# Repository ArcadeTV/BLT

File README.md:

## BLT (Button Layout Toggler)
### v20221101
#### ArcadeTV

| Part | Value            | Device           | Package             |
| ---- | ---------------- | ---------------- | ------------------- |
| CB1  | 100nF            | C-USC0805        | C0805               |
| CB2  | 100nF            | C-USC0805        | C0805               |
| CB3  | 100nF            | C-USC0805        | C0805               |
| D1   |                  | DUOLED2X5        | DUOLED2X5           |
| IC1  | 74HC4066D        | 74HC4066D        | SOIC127P600X175-14N |
| IC2  | 74HC4066D        | 74HC4066D        | SOIC127P600X175-14N |
| IC3  | ATTINY84V-10SSUR | ATTINY84V-10SSUR | SOIC127P600X175-14N |
| R1   | 220              | R-US_R0805       | R0805               |
| R2   | 220              | R-US_R0805       | R0805               |

---

#### Description:
This pcb remaps 4 buttons of a common-ground controller to two different layouts,
given that your controller has a 6-button-layout.
I was tired of having to reconfigure my arcade stick every time I switched games between
Street Fighter (6 Buttons) and Neo Geo (4 Buttons), so I came up with a solution that 
goes between the first four input signal lines from either a supergun or jamma harness.
The toggler pad on the pcb goes to a switch that connects to GND. This will trigger
the switching process and visual feedback can be added by an optional 2-color-LED.
Buttons 5 and 6 are not involved.

#### Microcontroller:
Please mind that the ATtiny84 microcontroller needs to be programmed
with the provided hex file.

#### PCB
Use the provided gerber files from the [releases tab](https://github.com/ArcadeTV/BLT/releases/latest) to order your pcb from your favorite manufacturer.

Eagle source files for editing also exist in this repository.

#### Installation
Populate the pcb after programming the ATtiny microcontroller.
Connect the lines coming from your supergun or jamma harness to the pads
marked with IN. Connect the button-lines to the pads marked OUT.
Connect a switch to the toggler-pad on the upper right of the pcb that
connects temporary to GND upon being pressed.
Install a 2-color-LED as you see fit. (Adjust R1 and R2 according to your LED specs)

```
Layout #1 (Street Fighter Style):
   .-.   .-.   .-.
  ( 1 ) ( 2 ) ( 3 )
   '-'   '-'   '-'
 .-.   .-.   .-.
( 4 ) ( 5 ) ( 6 )
 '-'   '-'   '-'

Layout #2 (Neo Geo Style):
   .-.   .-.   .-.
  ( 2 ) ( 3 ) ( 4 )
   '-'   '-'   '-'
 .-.   .-.   .-.
( 1 ) ( 5 ) ( 6 )
 '-'   '-'   '-'

```

Tested on a HORI Fighting Stick V3 (PS3 Version) that was rewired with a DB15 cable and connector
for use with a MINIGUN v2.5. The PS button on that stick was wired for toggling.

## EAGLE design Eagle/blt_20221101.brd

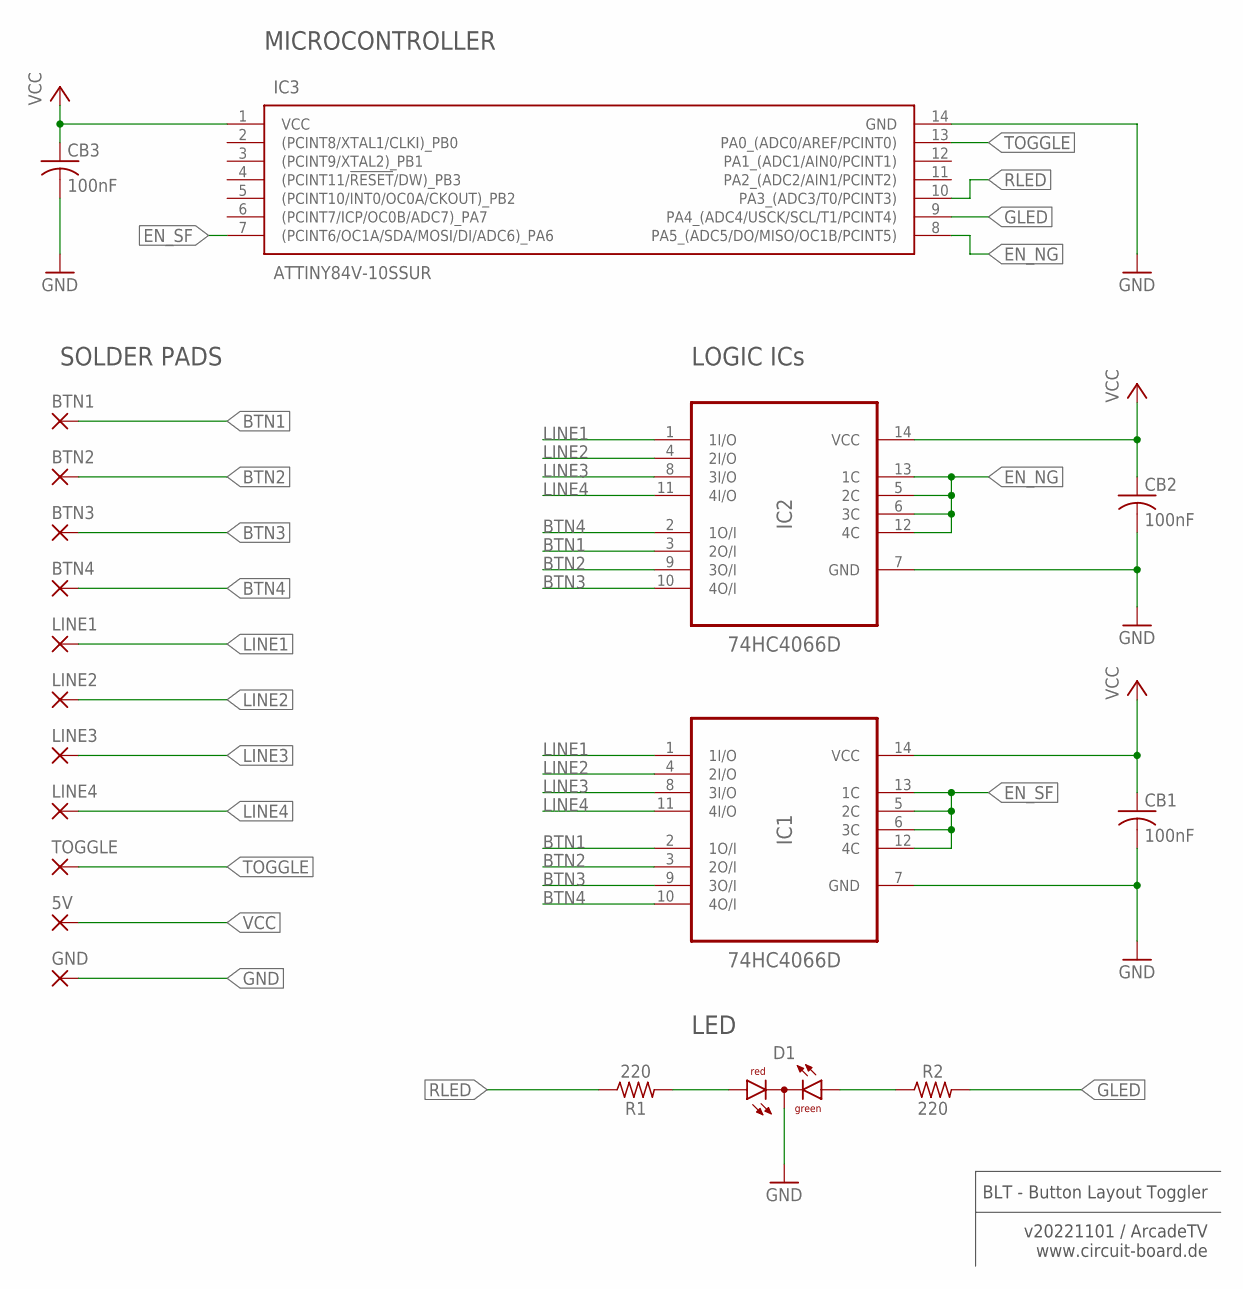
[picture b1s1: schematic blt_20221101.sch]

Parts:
5V: WIREPADSMD2,54-5,08; SMD2,54-5,08
BTN1, BTN2, BTN3, BTN4: WIREPADSMD2,54-5,08; SMD2,54-5,08
CB1, CB2, CB3: 100nF; C0805
D1: DUOLED2X5
GND: WIREPADSMD2,54-5,08; SMD2,54-5,08
IC1, IC2: 74HC4066D; SOIC127P600X175-14N
IC3: ATTINY84V-10SSUR; SOIC127P600X175-14N
LINE1, LINE2, LINE3, LINE4: WIREPADSMD2,54-5,08; SMD2,54-5,08
R1, R2: 220; R0805
TOGGLE: WIREPADSMD2,54-5,08; SMD2,54-5,08

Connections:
BTN1: BTN1.1, IC1.2 (1O/I), IC2.3 (2O/I)
BTN2: BTN2.1, IC1.3 (2O/I), IC2.9 (3O/I)
BTN3: BTN3.1, IC1.9 (3O/I), IC2.10 (4O/I)
BTN4: BTN4.1, IC1.10 (4O/I), IC2.2 (1O/I)
EN_NG: IC2.5 (2C), IC2.6 (3C), IC2.12 (4C), IC2.13 (1C), IC3.8 (PA5_(ADC5/DO/MISO/OC1B/PCINT5))
EN_SF: IC1.5 (2C), IC1.6 (3C), IC1.12 (4C), IC1.13 (1C), IC3.7 ((PCINT6/OC1A/SDA/MOSI/DI/ADC6)_PA6)
GLED: IC3.9 (PA4_(ADC4/USCK/SCL/T1/PCINT4)), R2.2
GND: CB1.2, CB2.2, CB3.2, D1.K (C), GND.1, IC1.7 (GND), IC2.7 (GND), IC3.14 (GND)
LINE1: IC1.1 (1I/O), IC2.1 (1I/O), LINE1.1
LINE2: IC1.4 (2I/O), IC2.4 (2I/O), LINE2.1
LINE3: IC1.8 (3I/O), IC2.8 (3I/O), LINE3.1
LINE4: IC1.11 (4I/O), IC2.11 (4I/O), LINE4.1
unnamed: D1.AR, R1.2
unnamed: D1.AG, R2.1
RLED: IC3.10 (PA3_(ADC3/T0/PCINT3)), R1.1
TOGGLE: IC3.13 (PA0_(ADC0/AREF/PCINT0)), TOGGLE.1
VCC: 5V.1, CB1.1, CB2.1, CB3.1, IC1.14 (VCC), IC2.14 (VCC), IC3.1 (VCC)

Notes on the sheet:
BLT - Button Layout Toggler v20221101 / ArcadeTV www.circuit-board.de
MICROCONTROLLER
SOLDER PADS
LOGIC ICs
LED

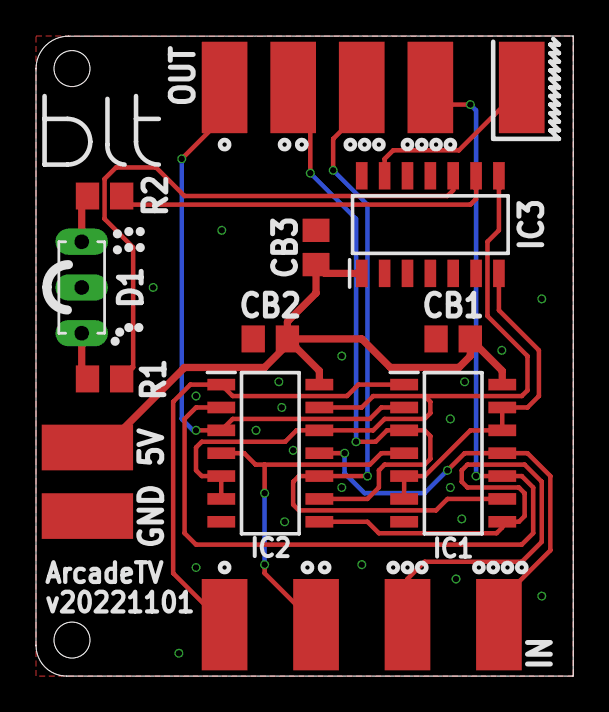
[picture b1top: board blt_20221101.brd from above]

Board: 2 copper layers, 29.8 x 35.6 mm, 20 parts (0 on the bottom side), 17 nets.

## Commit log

2022-11-02 Rename blt_20221101.brd to Eagle/blt_20221101.brd
2022-11-02 Rename blt_20221101.sch to Eagle/blt_20221101.sch
2022-11-02 Rename ATMEL-SWITCHCODE.ino to ATtiny/ATTINY84V-SWITCHCODE.ino
2022-11-02 Rename ATTINY84V_SWITCHCODE.hex to ATtiny/ATTINY84V_SWITCHCODE.hex
2022-11-02 Rename ATTINY84V_SWITCHCODE.readme.md to ATtiny/ATTINY84V_SWITCHCODE.readme.md
